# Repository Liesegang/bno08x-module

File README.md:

# BNO08x module

Akizuki [BNO055使用 9軸センサーフュージョンモジュールキット](https://akizukidenshi.com/catalog/g/g116996/) compatible BNO08x module board.
[BNO08x datasheet](https://www.ceva-ip.com/wp-content/uploads/BNO080_085-Datasheet.pdf)

**SUPPORT 3.3V ONLY**
Support qwiic connector.

|Solde Jumper|Function|
|--|--|
|J1|PS0 Low|
|J2|PS0 High|
|J3|PS1 Low|
|J4|PS1 High|
|J5|I2C Addr High|
|J6|I2C Addr LOW|

## Mode

|J1|J2|J3|J4|Mode|
|--|--|--|--|--|
|closed|open|closed|open|I2C|
|open|closed|closed|open|UART|

## I2C Addr

|JP5|JP6|I2C Addr|
|--|--|--|
|open|open|undefined|
|open|close|0x4A|
|close|open|0x4B|
|close|close|SHORT VCC AND GND!!!!!|

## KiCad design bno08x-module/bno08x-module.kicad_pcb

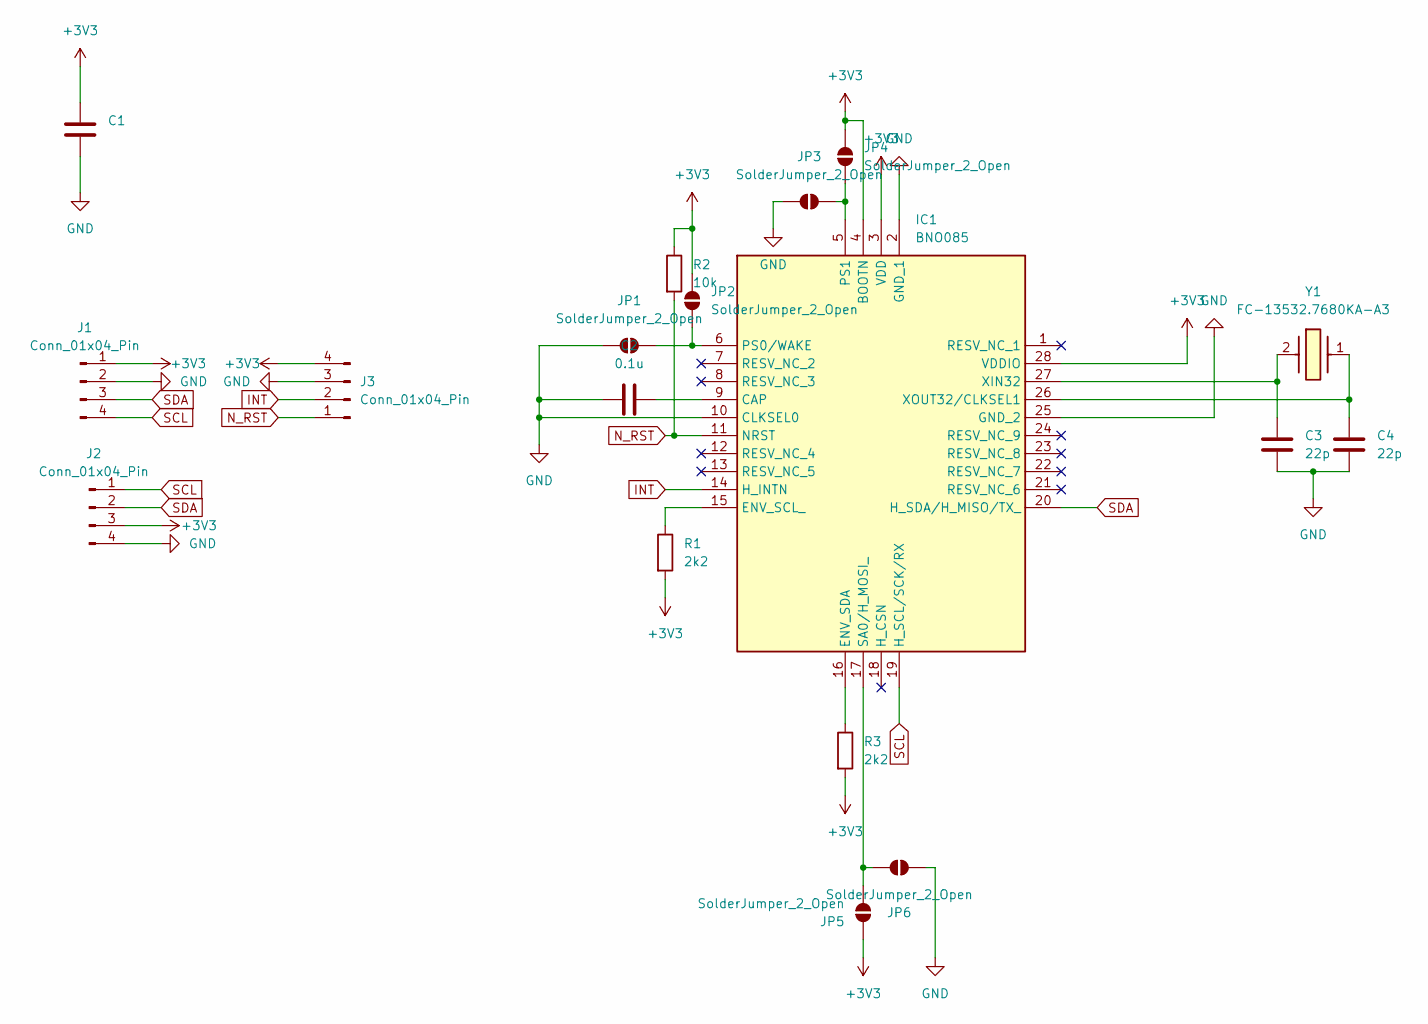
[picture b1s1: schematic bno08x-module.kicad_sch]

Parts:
C1, C2: 0.1u; C_0603_1608Metric
C3, C4: 22p; C_0603_1608Metric
IC1: BNO085; Manufacturer_Part_Number BNO085; Mouser Part Number 526-BNO085
J1, J3: Conn_01x04_Pin; PinHeader_1x04_P2.54mm_Vertical
J2: Conn_01x04_Pin; JST_SH_BM04B-SRSS-TB_1x04-1MP_P1.00mm_Vertical
JP1, JP2, JP3, JP4, JP5, JP6: SolderJumper_2_Open; R_0201_0603Metric
R1, R3: 2k2; R_0603_1608Metric
R2: 10k; R_0603_1608Metric
Y1: FC-13532.7680KA-A3; FC135327680KAA3; Manufacturer_Part_Number FC-13532.7680KA-A3

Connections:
+3V3: C1.1, IC1.3 (VDD), IC1.4 (BOOTN), IC1.28 (VDDIO), J1.1, J2.3, J3.4, JP2.2 (B), JP4.2 (B), JP5.2 (B), R1.2, R2.1, R3.2
GND: C1.2, C2.1, C3.2, C4.2, IC1.2 (GND_1), IC1.10 (CLKSEL0), IC1.25 (GND_2), J1.2, J2.4, J3.3, JP1.1 (A), JP3.1 (A), JP6.1 (A)
INT: IC1.14 (H_INTN), J3.2
N_RST: IC1.11 (NRST), J3.1, R2.2
unnamed: C2.2, IC1.9 (CAP)
unnamed: IC1.15 (ENV_SCL_), R1.1
unnamed: IC1.16 (ENV_SDA), R3.1
unnamed: IC1.6 (PS0/WAKE), JP1.2 (B), JP2.1 (A)
unnamed: IC1.5 (PS1), JP3.2 (B), JP4.1 (A)
unnamed: IC1.17 (SA0/H_MOSI_), JP5.1 (A), JP6.2 (B)
unnamed: C3.1, IC1.27 (XIN32), Y1.2 (CRYSTAL_2)
unnamed: C4.1, IC1.26 (XOUT32/CLKSEL1), Y1.1
SCL: IC1.19 (H_SCL/SCK/RX), J1.4, J2.1
SDA: IC1.20 (H_SDA/H_MISO/TX_), J1.3, J2.2

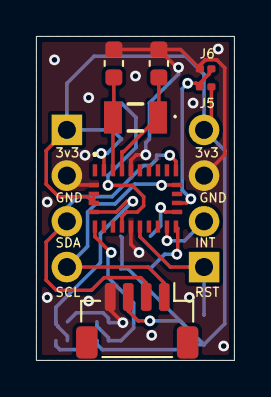
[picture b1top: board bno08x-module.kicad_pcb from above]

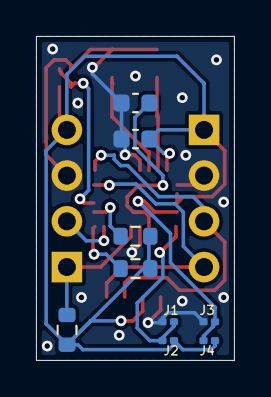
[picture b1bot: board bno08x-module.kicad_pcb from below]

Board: 2 copper layers, 11.0 x 18.0 mm, 18 parts (11 on the bottom side), 14 nets.
